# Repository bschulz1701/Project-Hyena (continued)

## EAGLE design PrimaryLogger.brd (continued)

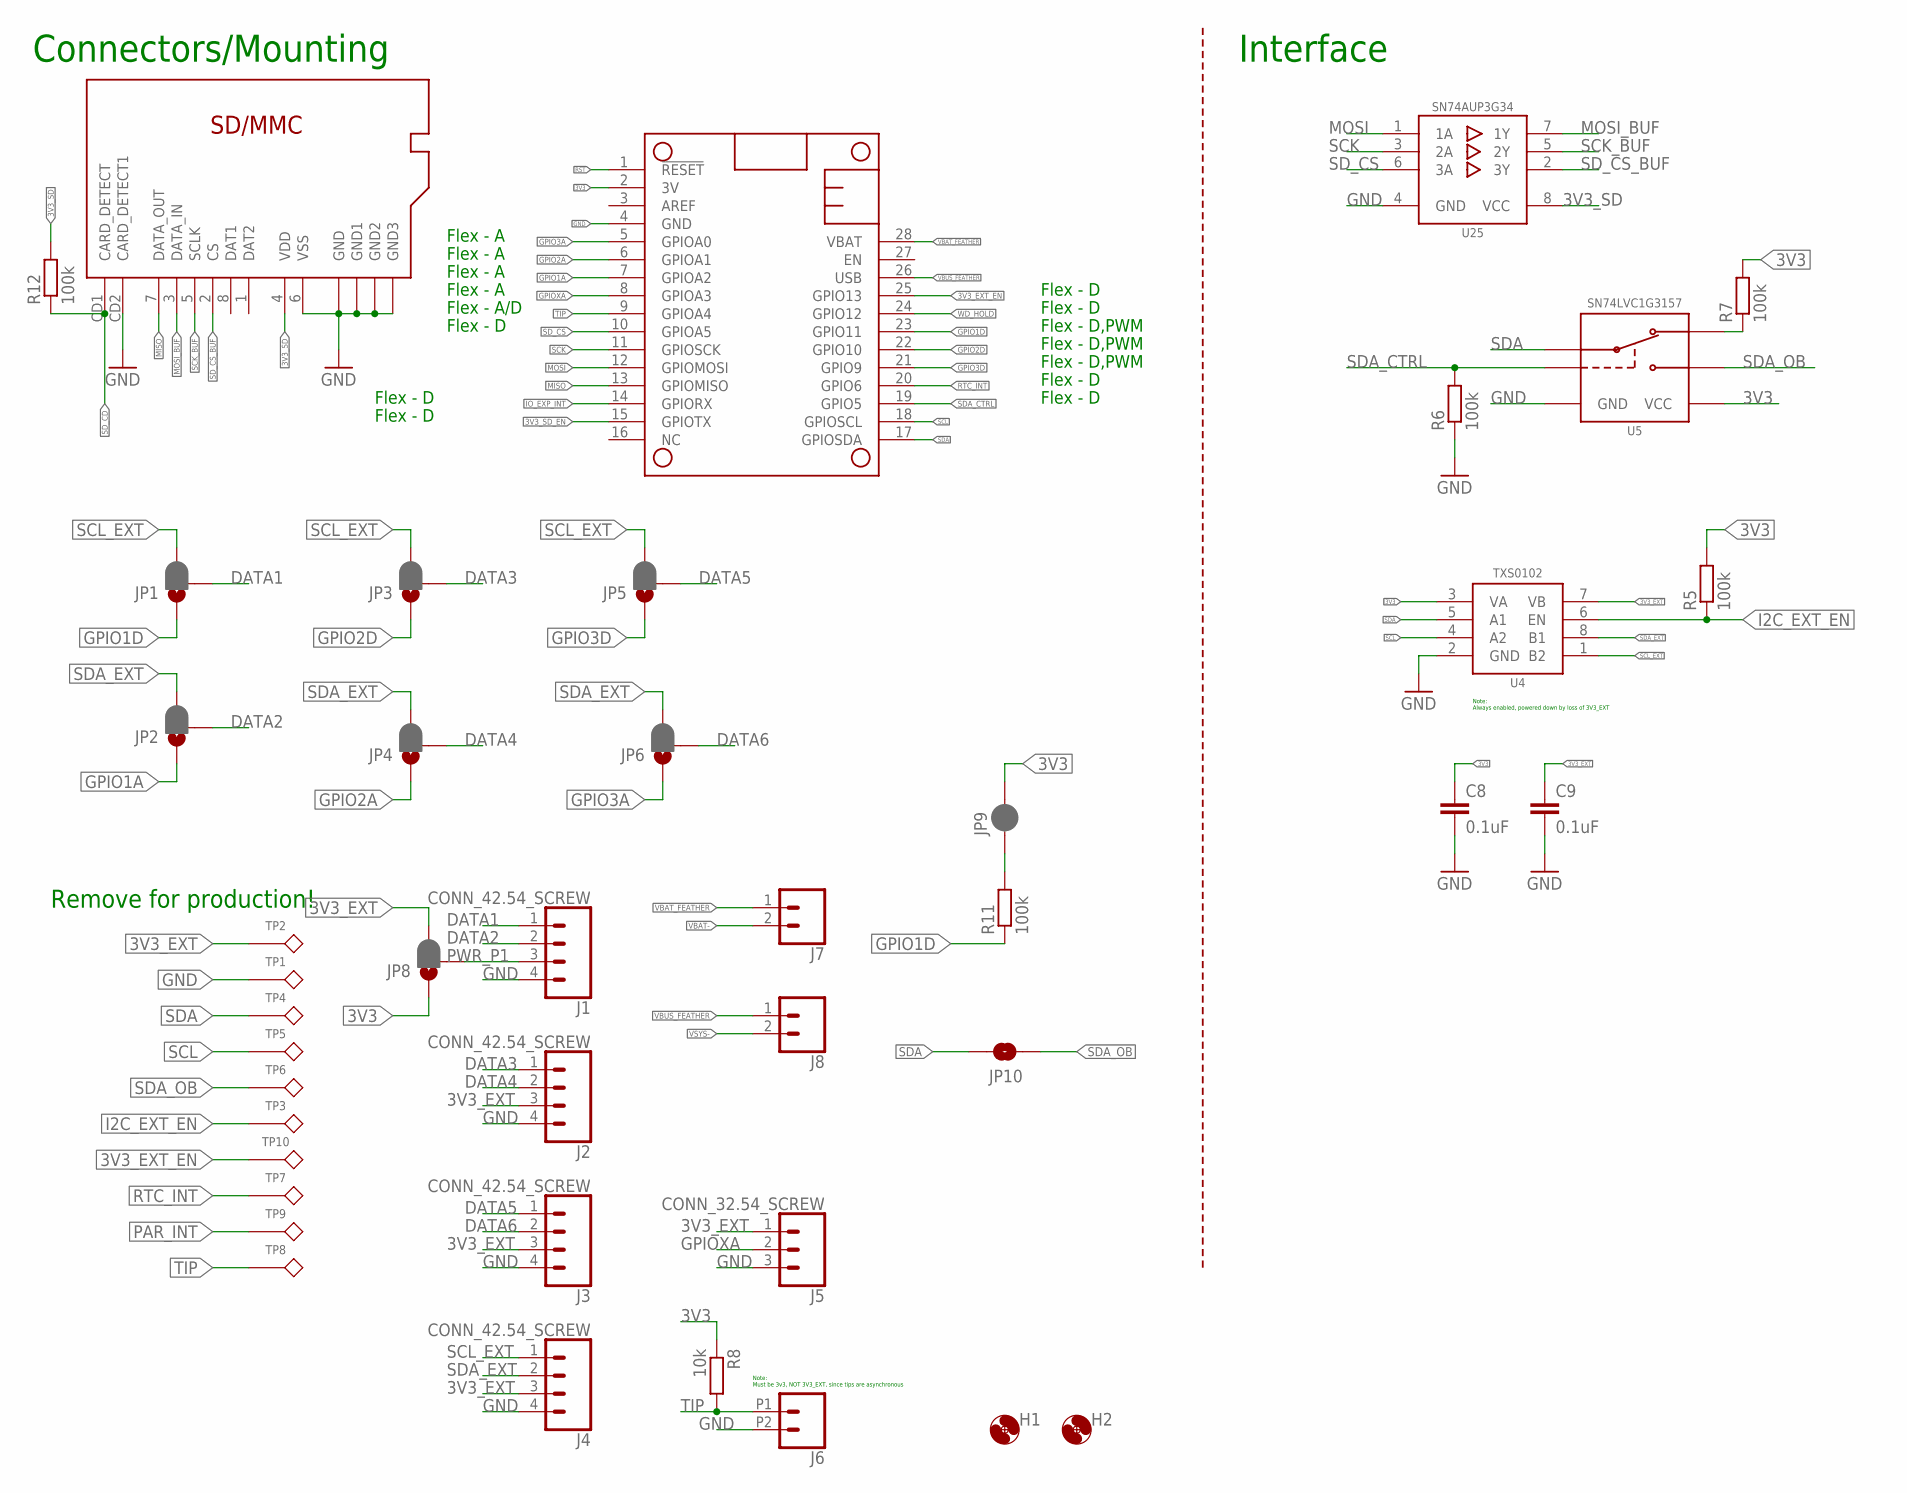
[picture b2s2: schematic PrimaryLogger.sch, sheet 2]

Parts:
C8, C9: 0.1uF; C0603
H1, H2: MOUNTING_HOLE4_NP; 4_40
J1, J2, J3, J4: CONN_42.54_SCREW; 1X04_SCREW
J5: CONN_32.54_SCREW; 1X03_SCREW
J6: CONN_022.54_SCREW_ROUND; 1X02_2.54_SCREWTERM_ROUND
J7, J8: CONN_023.5MM_ROUND; SCREWTERMINAL-3.5MM-2_ROUND
JP1, JP2, JP3, JP4, JP5, JP6, JP8: JUMPER-SMT_3_1-NC_PASTE_SILK; SMT-JUMPER_3_1-NC_PASTE_SILK
JP9: JUMPER-SMT_2_NC_PASTE_SILK; SMT-JUMPER_2_NC_PASTE_SILK
JP10: JUMPER-SMT_2_NO_SILK; SMT-JUMPER_2_NO_SILK
MS1: FEATHERWING_NODIM; FEATHERWING_DIM
R5, R6, R7, R11, R12: 100k; R0603
R8: 10k; R0603
SD1: MICRO_SD; CUSTOM-PARTS_SD_MICRO
TP1, TP2, TP3, TP4, TP5, TP6, TP7, TP8, TP9, TP10: TESTPOINTRCU; TESTPOINT_0603
U4: TXS0102DCU; DCU_(R-PDSO-G8)
U5: SN74LVC1G3157SC70; DCK_R-PDSO-G6
U25: SN74AUP3G34DCU; DCU_(R-PDSO-G8)

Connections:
3V3: C8.1, JP8.1, JP9.2, MS1.2 (3V), R5.2, R7.2, R8.1, U4.3 (VA), U5.5 (VCC); also elsewhere on the board
3V3_EXT: C9.1, J2.3, J3.3, J4.3, J5.1, JP8.3, TP2.1, U4.7 (VB); also elsewhere on the board
3V3_EXT_EN: MS1.25 (GPIO13), TP10.1; also elsewhere on the board
3V3_SD: R12.2, SD1.4 (VDD), U25.8 (VCC); also elsewhere on the board
3V3_SD_EN: MS1.15 (GPIOTX); also elsewhere on the board
DATA1: J1.1, JP1.2
DATA2: J1.2, JP2.2
DATA3: J2.1, JP3.2
DATA4: J2.2, JP4.2
DATA5: J3.1, JP5.2
DATA6: J3.2, JP6.2
GND: C8.2, C9.2, J1.4, J2.4, J3.4, J4.4, J5.3, J6.P2 (2), MS1.4 (GND), R6.1, SD1.6 (VSS), SD1.CD2 (CARD_DETECT1), SD1.GND@1 (GND), SD1.GND@2 (GND1), SD1.GND@3 (GND2), SD1.GND@5 (GND3), TP1.1, U4.2 (GND), U5.2 (GND), U25.4 (GND); also elsewhere on the board
GPIO1A: JP2.1, MS1.7 (GPIOA2)
GPIO1D: JP1.1, MS1.23 (GPIO11), R11.1
GPIO2A: JP4.1, MS1.6 (GPIOA1)
GPIO2D: JP3.1, MS1.22 (GPIO10)
GPIO3A: JP6.1, MS1.5 (GPIOA0)
GPIO3D: JP5.1, MS1.21 (GPIO9)
GPIOXA: J5.2, MS1.8 (GPIOA3)
I2C_EXT_EN: R5.1, TP3.1, U4.6 (EN); also elsewhere on the board
IO_EXP_INT: MS1.14 (GPIORX); also elsewhere on the board
MISO: MS1.13 (GPIOMISO), SD1.7 (DATA_OUT)
MOSI: MS1.12 (GPIOMOSI), U25.1 (1A)
MOSI_BUF: SD1.3 (DATA_IN), U25.7 (1Y)
unnamed: R7.1, U5.3 (B1)
unnamed: JP9.1, R11.2
PAR_INT: TP9.1; also elsewhere on the board
PWR_P1: J1.3, JP8.2
RST: MS1.1 (!RESET); also elsewhere on the board
RTC_INT: MS1.20 (GPIO6), TP7.1; also elsewhere on the board
SCK: MS1.11 (GPIOSCK), U25.3 (2A)
SCK_BUF: SD1.5 (SCLK), U25.5 (2Y)
SCL: MS1.18 (GPIOSCL), TP5.1, U4.4 (A2); also elsewhere on the board
SCL_EXT: J4.1, JP1.3, JP3.3, JP5.3, U4.1 (B2)
SDA: JP10.2, MS1.17 (GPIOSDA), TP4.1, U4.5 (A1), U5.4 (A)
SDA_CTRL: MS1.19 (GPIO5), R6.2, U5.6 (S)
SDA_EXT: J4.2, JP2.3, JP4.3, JP6.3, U4.8 (B1)
SDA_OB: JP10.1, TP6.1, U5.1 (B2); also elsewhere on the board
SD_CD: R12.1, SD1.CD1 (CARD_DETECT); also elsewhere on the board
SD_CS: MS1.10 (GPIOA5), U25.6 (3A)
SD_CS_BUF: SD1.2 (CS), U25.2 (3Y)
TIP: J6.P1 (1), MS1.9 (GPIOA4), R8.2, TP8.1
VBAT-: J7.2; also elsewhere on the board
VBAT_FEATHER: J7.1, MS1.28 (VBAT); also elsewhere on the board
VBUS_FEATHER: J8.1, MS1.26 (USB); also elsewhere on the board
VSYS-: J8.2; also elsewhere on the board
WD_HOLD: MS1.24 (GPIO12); also elsewhere on the board

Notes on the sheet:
Note: Must be 3v3, NOT 3V3_EXT, since tips are asynchronous
Remove for production!
Flex - A
Flex - A/D
Flex - D
Flex - D,PWM
Note: Always enabled, powered down by loss of 3V3_EXT
Connectors/Mounting
Interface

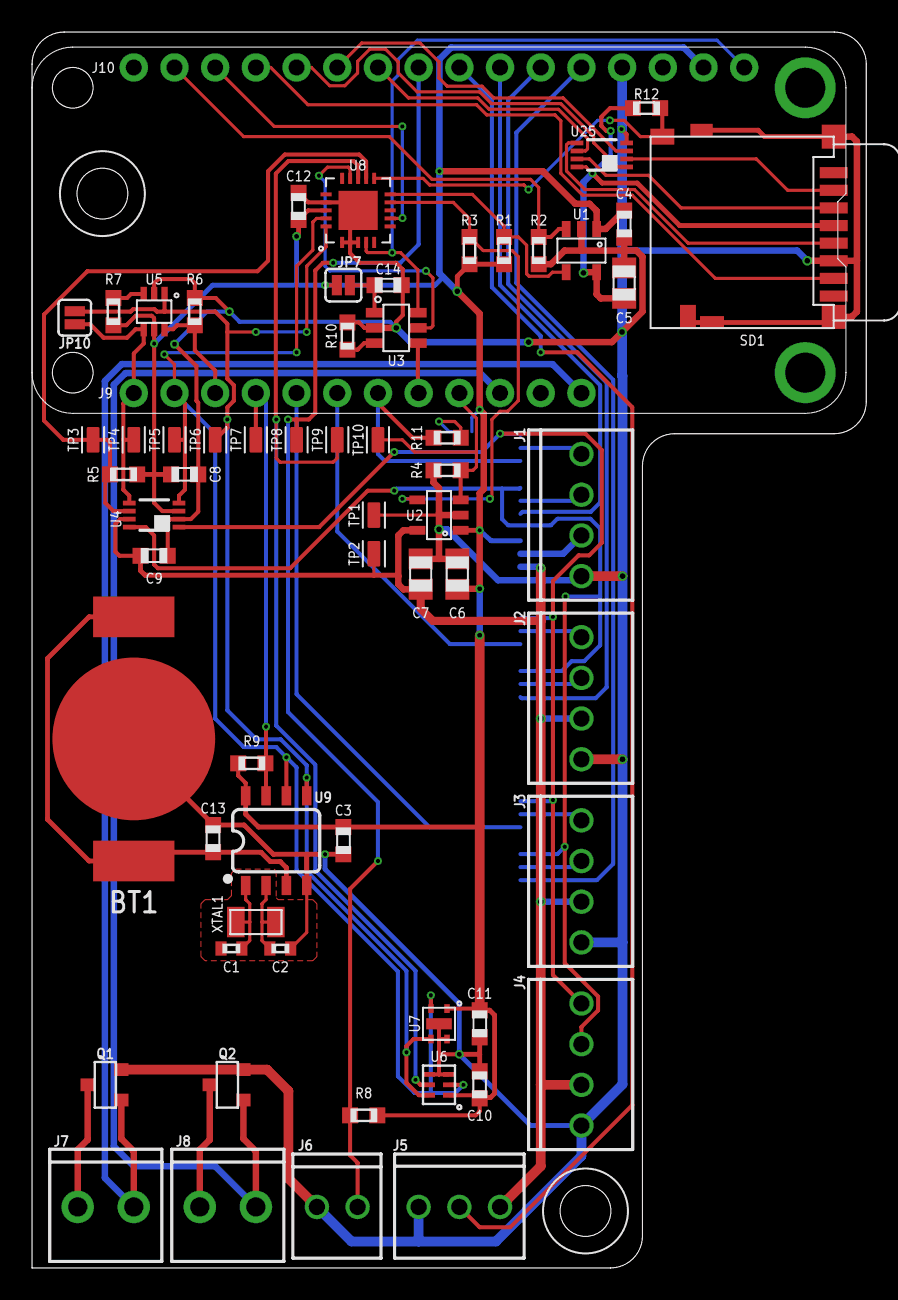
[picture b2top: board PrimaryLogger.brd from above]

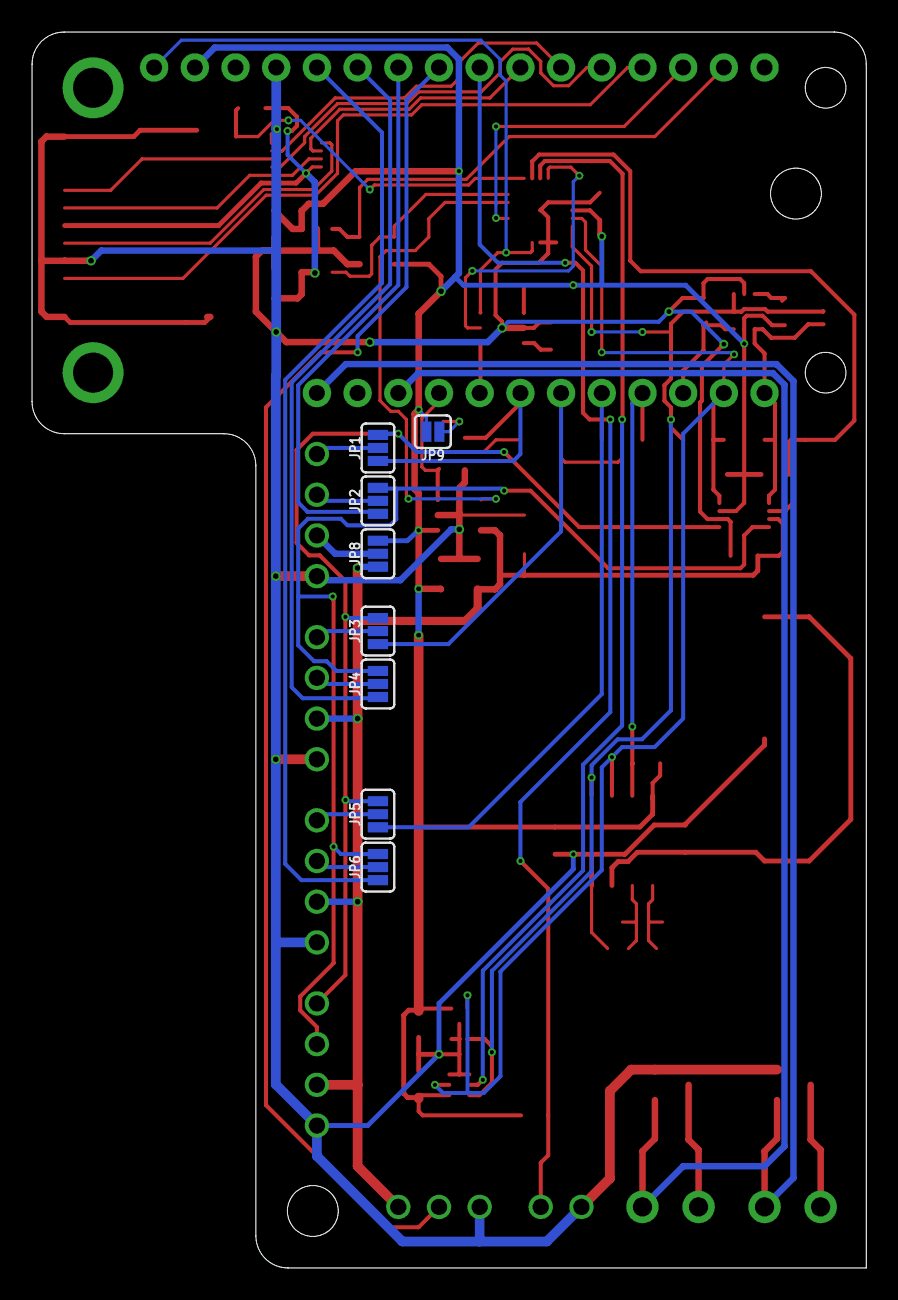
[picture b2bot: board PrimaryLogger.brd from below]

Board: 2 copper layers, 52.1 x 77.1 mm, 72 parts (8 on the bottom side), 55 nets.

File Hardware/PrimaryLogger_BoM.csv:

"Qty","Value","Device","Package","Parts","Description","DIGIKEY","DISP","MF","MPN","VALUE","VALUE_PART",
"1","","CONN_022.54_SCREW_ROUND","1X02_2.54_SCREWTERM_ROUND","J6","Genaric 2 terminal header","ED10561-ND","","OnShore","OSTVN02A150","","",
"2","","CONN_023.5MM_ROUND","SCREWTERMINAL-3.5MM-2_ROUND","J7, J8","Genaric 2 terminal header","ED2635-ND","","OnShore","OSTTE020161","","",
"2","","MOUNTING_HOLE4_NP","4_40","H1, H2","Genaric Mechanical Mounting Hole","DNP","","N/A","DNP","","",
"7","0.1uF","C-EU0.1UFC0603","C0603","C3, C8, C9, C11, C12, C13, C14","CAPACITOR, European symbol","490-6051-1-ND","","Murata","GCM188R71E104KA57D","","",
"11","100k","R-EU_100KR0603","R0603","R1, R2, R3, R4, R5, R6, R7, R9, R10, R11, R12","RESISTOR, European symbol","311-100KHRCT-ND","","Yageo","RC0603FR-07100KL","","100k",
"1","100k","R-EU_10KR0603","R0603","R8","RESISTOR, European symbol","311-10.0KHRCT-ND","","Yageo","RC0603FR-0710KL","","10k",
"3","10uF","C-EU10UFC0805","C0805","C5, C6, C7","CAPACITOR, European symbol","490-6473-6-ND","","Murata","GRM21BR61C106KE15K","","",
"2","1uF","C-EU1UFC0603","C0603","C4, C10","CAPACITOR, European symbol","587-1251-1-ND","","Yaiyo Yuden","EMK107BJ105KA-T","","",
"2","6pF","C-EU6PFC0402","C0402","C1, C2","CAPACITOR, European symbol","490-3104-1-ND","","Murata","GJM1555C1H6R0CB01D","","",
"1","BATTERY_COIN12MM","BATTERY_COIN12MM","LINX_BAT-HLD-012-SMT","BT1","Coin Cell Battery Holder","BAT-HLD-012-SMT-ND","","Linx","BAT-HLD-012-SMT","","",
"1","CONN_32.54_SCREW","CONN_32.54_SCREW","1X03_SCREW","J5","Genaric 3 terminal header","ED10562-ND","","On Shore","OSTVN03A150","","",
"4","CONN_42.54_SCREW","CONN_42.54_SCREW","1X04_SCREW","J1, J2, J3, J4","Genaric 4 terminal header","ED10563-ND","","On Shore","OSTVN04A150","","",
"1","CRYSTAL3.2X1.5","CRYSTAL3.2X1.5","CRYSTAL_3.2X1.5_2-SMD","XTAL1","Crystal Oscilator","535-11937-1-ND","","ABS07-120-32.768KHZ-T","Abracon","","",
"2","DMG3404","MOSFET-NCH-DMG3404L","SOT23-3","Q1, Q2","N-channel MOSFETs","DMG3404L-7DICT-ND","","Diodes Incorporated","DMG3404L-7","DMG3404","",
"1","FEATHERWING_NODIM","FEATHERWING_NODIM","FEATHERWING_DIM","MS1","","","","","","","",
"2","JUMPER-SMT_2_NC_PASTE_SILK","JUMPER-SMT_2_NC_PASTE_SILK","SMT-JUMPER_2_NC_PASTE_SILK","JP7, JP9","Normally closed solder jumper","DNP","","N/A","N/A","","",
"1","JUMPER-SMT_2_NO_SILK","JUMPER-SMT_2_NO_SILK","SMT-JUMPER_2_NO_SILK","JP10","Normally open jumper","DNP","","N/A","N/A","","",
"7","JUMPER-SMT_3_1-NC_PASTE_SILK","JUMPER-SMT_3_1-NC_PASTE_SILK","SMT-JUMPER_3_1-NC_PASTE_SILK","JP1, JP2, JP3, JP4, JP5, JP6, JP8","Normally closed solder jumper (1 of 2 connections)","DNP","","N/A","N/A","","",
"1","MCP23008QFN","MCP23008QFN","QFN20","U8","MCP23008 - I2C I/O Expander, 8 bit wtih interrupt and reset","MCP23008T-E/MLCT-ND","","Microchip","MCP23008T-E/ML","","",
"1","MCP7940SOIC","MCP7940SOIC","SO08","U9","MCP7940 - RTC","MCP7940N-I/SN-ND","","Microchip","MCP7940N-I/SN","","",
"2","MIC2005","MIC2005","SOT23-5","U1, U2","MIC2005 - Hight Side Load Switch, with Fixed Current Limit","576-3462-1-ND","MIC2005","Microchip","MIC2005A-1YM5-TR","","",
"1","MICRO_SD","MICRO_SD","CUSTOM-PARTS_SD_MICRO","SD1","Micro SD Card - Card Detect, Exposed leads for non-reflow soldering","114-00841-68-1-ND","","Amphenol","114-00841-68","","",
"1","SHTC3DFN","SHTC3DFN","DFN_4_2X2","U7","SHTCx - Digital Humidity and Temperature Sensor","1649-1100-1-ND","SHTC3","Sensirion","SHTC3","","",
"1","SN74AUP3G34DCU","SN74AUP3G34DCU","DCU_(R-PDSO-G8)","U25","SN74AUP3G34 - Logic Buffer","296-25595-1-ND","","TI","SN74AUP3G34DCUR","","",
"1","SN74LVC1G3157SC70","SN74LVC1G3157SC70","DCK_R-PDSO-G6","U5","SN74LVC1G3157 - SPDT Analog Switch","296-14909-1-ND","SN74LVC1G3157","TI","SN74LVC1G3157DCKR","","",
"1","TCS3400","TCS3400","TCS3400","U6","TCS3400 - Ambient Multi-Band Light Sensor with I2C Interface","TCS34003FNMCT-ND","","AMS","TCS34003FNM","","",
"10","TESTPOINTRCU","TESTPOINTRCU","TESTPOINT_0603","TP1, TP2, TP3, TP4, TP5, TP6, TP7, TP8, TP9, TP10","","A106145CT-ND","","TE Connectivity","RCU-0C","","",
"1","TPL5010DDC","TPL5010DDC","DDC_R-PDSO-G6","U3","TPL5010 - Nano-Power System Timer with Watchdog Functionality","296-38829-1-ND","","TI","TPL5010DDCT","","",
"1","TXS0102DCU","TXS0102DCU","DCU_(R-PDSO-G8)","U4","TXS0102 - 2 Channel Bidirectional Voltage Level Translator","296-21931-1-ND","","TI","TXS0102DCUR","","",

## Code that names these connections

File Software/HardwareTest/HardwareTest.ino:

#include <SPI.h>
#include <Wire.h>
#include <MCP7940.h>
#include <SD.h>
//FIX Make random function??

boolean Debug = false; //FIX!!
char ReadArray[25] = {0};

// namespace Pins { //Use for Boron
// 	constexpr uint16_t WD_HOLD  = 7;
// 	constexpr uint16_t EXT_EN   = 8;
// 	constexpr uint16_t SD_EN    = 9;
// 	constexpr uint16_t SD_CS    = 14;
// 	constexpr uint16_t SDA_CTRL = 2;
// 	constexpr uint16_t TIP      = 15;
// 	constexpr uint16_t GPIOXA 	= 16;
// 	constexpr uint16_t Clock_INT 	= 2;
// }

namespace Pins { //Use for Feather M0 Express
	constexpr uint16_t WD_HOLD  = 12;
	constexpr uint16_t EXT_EN   = 13;
	constexpr uint16_t SD_EN    = 1;
	constexpr uint16_t SD_CS    = 19;
	constexpr uint16_t SDA_CTRL = 5;
	constexpr uint16_t TIP      = 18;
	constexpr uint16_t GPIOXA 	= 17;
	constexpr uint16_t Clock_INT 	= 6;
}

//////////////////////////////////////I2C/////////////////////////////////////
uint8_t ExpectedAddresses[] = {0x20, 0x39, 0x6F, 0x70}; //Define the I2C devices which should be present on Hyena 
uint8_t NumDevices = 4; //This is the number of I2C devices expected 

////////////////////////////////////SD////////////////////////////////////////
char FileNameC[11]; //Used for file handling
boolean SD_Init = false;

////////////////////////////////////CLOCK//////////////////////////////////////
MCP7940 Clock; // Instantiate Clock

void setup() {
	Serial.begin(115200); //Begin fast serial 
	pinMode(Pins::EXT_EN, OUTPUT);
	digitalWrite(Pins::EXT_EN, HIGH); //Turn on external power 
	while(!Serial); //Wait for serial to start //DEBUG!
	Wire.begin(); //Start I2C module
  

}

void loop() {
	Serial.println("Begin Test...");
	Serial.print("SD:\t");
	Serial.println(BoolToString(TestSD()));
	Serial.print("I2C:\t");
	Serial.println(BoolToString(TestI2C()));
	Serial.print("Sense:\t");
	Serial.println(BoolToString(TestSensors()));
	Serial.print("RTC:\t");
	Serial.println(BoolToString(TestClock()));
	Serial.print("Current Time:\t");
	Serial.println(Clock.GetTime(MCP7940::Format::ISO_8601)); //FIX! //Grab time from Clock)
	Serial.println("...End Test");
	while(1);
}

bool TestSD() 
{
	pinMode(Pins::SD_EN, OUTPUT); //Ensure EN pin is setup as output
	digitalWrite(Pins::SD_EN, HIGH); //Set enable pin to turn on power

	boolean SDError = false;
	pinMode(Pins::SD_CS, OUTPUT);
	SPI.beginTransaction(SPISettings(4000000, MSBFIRST, SPI_MODE0));
	// SPI.setDataMode(SPI_MODE0);
	// SPI.setClockDivider(SPI_CLOCK_DIV2); //Sts SPI clock to 4 MHz for an 8 MHz system clock

	if(!SD_Init) {
		if (!SD.begin(Pins::SD_CS)) {
			if(Debug) Serial.println("Failed Init");
			SDError = true; 
			return SDError;
		}
		if(Debug) Serial.println("Initialized");
		SD_Init = true;
	}
	String FileName = "HWTest";

	(FileName + ".txt").toCharArray(FileNameC, 11);
	SD.remove(FileNameC); //Remove any previous files

	randomSeed(millis()); //Seed with a random number to try to endsure randomness
	int RandVal = random(30557); //Generate a random number between 0 and 30557 (the number of words in Hamlet)
	char RandDigits[5] = {0};
	sprintf(RandDigits, "%d", RandVal); //Convert RandVal into a series of digits
	int RandLength = (int)((ceil(log10(RandVal))+1)*sizeof(char)); //Find the length of the values in the array
//	Serial.print("Random Digits:"); //DEBUG!
//	for(int p = 0; p < 5; p++) { //DEBUG!
//	Serial.print(RandDigits[p]);
//	}
//	Serial.println(""); //DEBUG!

	File DataWrite = SD.open(FileNameC, FILE_WRITE);
	if(DataWrite) {
		DataWrite.println(RandVal);
		DataWrite.println("\nHe was a man. Take him for all in all.");
		DataWrite.println("I shall not look upon his like again.");
		DataWrite.println("-Hamlet, Act 1, Scene 2");
	}
	DataWrite.close();

	if(Debug){
		Serial.print("Random Value = "); Serial.println(RandVal);
	}

	char TestDigits[5] = {0};
	File DataRead = SD.open(FileNameC, FILE_READ);
	if(DataRead) {
		DataRead.read(TestDigits, RandLength);

		if(Debug){
		  Serial.print("Recieved Value = ");
		}
		for(int i = 0; i < RandLength - 1; i++){ //Test random value string
			if(Debug) Serial.print(TestDigits[i]);
			if(TestDigits[i] != RandDigits[i]) {
				SDError = true;
				Serial.print("x"); //DEBUG!
				Serial.print(RandDigits[i]);
			}
		}
		if(Debug) Serial.println("");

		if(Debug) {
		//      byte Data = DataRead.read();
			Serial.println("SD Test Data:");
			while(DataRead.available()) {
				Serial.write(DataRead.read());
			//        Data = DataRead.read();
			}
		}
	}
	DataRead.close();

	if(Debug) Serial.println("");

	SD.remove(FileNameC); //Remove dummy file created 

	return SDError;
}

bool TestI2C() //Test against fixed list 
{
	pinMode(Pins::SDA_CTRL, OUTPUT); //Setup SDA control as an output
	digitalWrite(Pins::SDA_CTRL, HIGH); //Set turn on on board SDA

	for(int i = 0; i < NumDevices; i++) {
		Wire.beginTransmission(ExpectedAddresses[i]);
		Wire.write(0x00);
		if(Wire.endTransmission() != 0) {
			Serial.println(ExpectedAddresses[i]);
			return 1; //Return failure if any device fails
		}
	}

	return 0; //If all devices return 0, then return passing state 
}

bool TestClock()
{
	bool Clock_Error = 1; //Default error
  pinMode(Pins::SDA_CTRL, OUTPUT); //Setup SDA control as an output
  digitalWrite(Pins::SDA_CTRL, HIGH); //Set turn on on board SDA
	pinMode(Pins::Clock_INT, INPUT); //Setup Clock pin as input
	// Serial.print("Start Time:\t");
	// Serial.println(Clock.GetTime(MCP7940::Format::ISO_8601)); //FIX! //Grab time from Clock)
  Clock.Begin();
  Clock.ClearAlarm(0);
  Clock.ClearAlarm(1);
  Clock.SetMode(MCP7940::Mode::Inverted); //Use dual alarm setup 
  Clock.SetTime(2021, 06, 10, 2, 12, 0, 0); //Set arbitrary time (incept date) //DEBUG!
	Clock.SetAlarm(5); //Set an alarm for 5 seconds from now

	unsigned long LocalTime = millis();
  // Serial.print("Alarm State = "); 
  // Serial.println(Clock.ReadAlarm());
	while(digitalRead(Pins::Clock_INT) != HIGH && (millis() - LocalTime < 7000)); //Wait for Clock to trigger, or 7 seconds to go by 
  // Serial.print("Alarm State = "); 
  // Serial.println(Clock.ReadAlarm());
	if(millis() - LocalTime < 7000 && (millis() - LocalTime > 3000)) { //Ensure time passed is greater than 3 seconds, less than 7 seconds 
		// Serial.print("End Time:\t");
		// Serial.println(return Clock.GetTime(MCP7940::Format::ISO_8601)); //FIX! //Grab time from Clock)
		if(Clock.ReadAlarm(0) == true) Clock_Error = 0; //Clear error
		else Clock_Error = 1; //Set error flag if interrupt bit not setg
	}
	else {
		// Serial.println("ERROR: No Alarm!");
		Clock_Error = 1; //Set alarm flag
	}

	return Clock_Error; //Return the resulting state
}

bool TestSensors()
{
	return 0; //FIX! 
}

String BoolToString(bool State)
{
	String Vals[] = {"Pass", "Fail"};
	return Vals[State]; //Return appropriate value based on State
}

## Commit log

2020-02-12 Added design documentation
2020-02-13 Initial schematic capture for primary logger
2020-02-14 Continued layout progress
2020-02-15 Continued layout and preliminary board capture
2020-02-17 BETA preliminary layout
2020-02-18 Added gerbers and BoM for prelim quote
2020-02-19 Updated BoM for advanced circuits quote
2020-02-19 Minor updates to layout
    Added silk screen, added test points, other minor edits
2020-02-21 Minor updates to make consistent with Soil Symbiont
    Changed 10uF to 0805 and mux to SC-70 package
2020-02-22 Minor part value and silkscreen updates, gerbers generated
2020-03-06 Added design visuals
2020-03-06 Minor silk screen update, post v0.0
2020-03-13 Added I2C address info to schematic
2020-03-13 Added pin definition documentation to README
2020-03-13 Added IO Expander pin info to readme
2020-03-14 Minor hardware readme update
2020-03-16 Updated testing documentation
2020-03-19 Updated testing, documentation and organization
2020-04-20 Updated for v0.1, ready for fab
2020-05-07 Updated part numbers
2020-05-07 Fixed silk screen issue, updated version number and BoM
    Fixed minor silk screen issue in v0.1 (duplicate "PORT1" text on bottom), updated version number in schematic, generated new BoM with updated part numbers
2020-07-15 Updated parts for BoM, moved designators, changed R41
    Updated part numbers to generate BoM, moved `R11` designator and changed `R41` to be `R12` to match ordering of rest of board (was carry over from Resnik I think)
2020-07-15 Added HardwareTest script
2020-10-12 Changes in testing readme to fix links
2020-12-14 Gerber and part updates
    Added Gerber files for Advanced Circuits order, minor changes to part numbers and BoMs
2020-12-14 Documentation and folder structure updates
    Moved around the folder structure, added board pictures, and added to README
2020-12-14 Further documentation updates
    Moved production files around, updated BoM in hardware and part libraries links to support that (DNP values issue)
2020-12-15 Added README for Documents and Software
    Added readme files for all first level folders, also changed folder structure within Documents
2021-04-01 Added cropped board image
2021-04-01 Added test scripts
2021-04-01 Cleaned up schematic and made new PDF - final v0.2
2021-04-01 Changed production folder structure, cleanup
2021-04-01 Added LED support for v0.3
    Schematic capture and preliminary layout of LED indicator
2021-04-02 Update README.md
    "Roadmap" is overloaded w/ software world
2021-04-06 Updated IO expander to SSOP package
2021-04-07 Added Niagara, jumpers, power connector
2021-04-13 Cleanup and gerbers for v0.3A
    Cleanup of schematic and layout for v0.3A design
2021-04-16 Updated part values for BoM generation
2021-04-16 Generated BoM for v0.3
2021-05-10 Minor updates v0.4A sent to fab
    Fixed layout issues and changed power topology for I2C buffer
2021-05-18 v1.0 Updates
    Changed pinout and added connector to support preliminary talon development
2021-06-02 Added part testing info for alternative crystal
    Added testing information about testing alternative crystal in Testing README
2021-06-02 Added build files for v0.4A board
    Added build files for v0.4A board for Caltronics quote, gerbers, pick and place, and zipped quote file
2021-06-02 Fixed formatting of Testing README
2022-03-30 Added license
